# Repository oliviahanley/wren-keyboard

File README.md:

# Wren Keyboard

## Table of Contents
- [Introduction](https://github.com/oliviahanley/wren-keyboard#introduction)
- [2.0 Update](https://github.com/oliviahanley/wren-keyboard#2.0-update)
- [Controller](https://github.com/oliviahanley/wren-keyboard#controller)
- [PCB](https://github.com/oliviahanley/wren-keyboard#pcb)
- [Case and Plate](https://github.com/oliviahanley/wren-keyboard#case-and-plate)
- [Software](https://github.com/oliviahanley/wren-keyboard#software)
- [Cost Estimates and Purchasing](https://github.com/oliviahanley/wren-keyboard#cost-estimates-and-purchasing)
- [BOM](https://github.com/oliviahanley/wren-keyboard#bom)
- [Build Guide](https://github.com/oliviahanley/wren-keyboard#build-guide)

## Introduction
The Wren is a split ergonomic system keyboard. It takes heavy inspiration from the Lily58, [Afternoon Labs' Breeze](https://afternoonlabs.com/breeze/), and [SplitKB's Kyria](https://blog.splitkb.com/blog/introducing-the-kyria) with a Corne-ish layout.

Before this, my primary keyboard had been Prime Keyboards' prime_o, before which I used a handwired Planck. On both I made pretty heavy use of the numpad. I grew to appreciate the prime\_o's physical one, though, mostly because I spend a lot of time in Excel at my day job and like using the mouse and numpad simultaneously. I've been wanting to switch to ergo for a while, but I was annoyed by the thought of having to use a separate numpad to recreate that experience. This project was an attempt to solve that problem.

My original design simply incorporated a southpaw numpad. After some feedback, though, I decided to reinvent it as a more adaptable design. The repository includes a universal PCB (incorporating break-away tabs) and plates to make four boards, each reversible:
- A Lilly58/Kyria-inspired split board, with no extra keys;
- An extended layout with a 4x4 numpad;
- An extended layout with a traditional nav cluster; and
- A small 4x4 macropad (nicknamed Egg).

Each of these boards (besides the macropad) can be combined with the others in a split setup, so users can take their pick of a right or left nav cluster/numpad or combine both in the same board. You could even just use two of the basic boards together for a more traditional layout, though I'm sure there are more elegant designs out there for that.

## 2.0 Update
The 2.0 release includes several major changes, including:
- A 3D printable (or CNCable) case with two height variations
- Nice!Nano compatibility with battery plug and ZMK compatibility
- Nice!View support
- Support for hot-swap sockets in addition to soldered switches
- Choc v1 variant
- Optional display cover
- Better design and documentation for the Egg
- Flip-flop footprints for the MCU

## Controller
The Wren uses a Pro Micro-compatible footprint, but is designed around the Elite-C or nice!Nano's extra I/O pins. With just a Pro Micro, the outer column and nice!view won't work.

## PCB
The PCB uses reversible, MX and choc compatible footprints with hot-swap support.

The PCB is specifically designed around rotary encoders with a diameter less than 0.5". I'm using Kilo 50 sized knobs, but others in a similar size class will work well, too.

## Case and Plate
This repository includes a top and bottom plate designed around M2 screws and standoffs. The bottom plate can be manufactured out of FR4 PCB material by any manufacturer; this will likely be the most cost-effective option. The top plate cannot be manufactured by my preferred PCB fabricator, JLCPCB, but your milage may vary. Instead, I used the .eps files included in the [Case folder](https://github.com/oliviahanley/wren-keyboard/tree/main/Case) to have my top plates manufactured in stainless steel by SendCutSend. In my experience these plates are an extremely tight fit around Kailh Box switches, but considering these aren't hot-swap that's an acceptable trade-off for me.

To make a complete case, you'll need 7 M2 spacers (5 for the plain board), a top plate, and a bottom plate.

There's also a 3D-printed bottom case. This uses the top plate and PCB without the bottom plate. \<\<MORE HERE\>\>

## Software
Tested code for this board is in the [main QMK repository](https://github.com/qmk/qmk_firmware/pull/14570). Thanks so much to [noroadsleft](https://github.com/qmk/qmk_firmware/pull/16462) for getting QMK configurator working! To build a hex file with the default keymap, use the following code after setting up your [QMK build environment](https://docs.qmk.fm/#/newbs_getting_started):

```
qmk compile -kb wren -km default
```

This can be flashed to your keyboard [in the usual way](https://docs.qmk.fm/#/newbs_flashing). The push-button below the microcontroler will put the keyboard into DFU mode. 

When customizing your keymap, note that the matrix includes all keys that would be present in a numpad-numpad pair. In other words, even if the left side of your physical keyboard lacks a numpad, your keymap.c file will include those keys. Feel free to either mark all those keys with a KC_NO keycode or leave them as-is--it's not like you can press them anyway :). As well, if you'd like to plug your USB cable into the right half instead of the default left, add the following to your config.h:

```
#define MASTER_RIGHT
```

\<\<ZMK INFO HERE\>\>

## Cost Estimates and Purchasing <\<\UPDATE\>\>
It should be relatively affordable to have these boards manufactured. Here are my costs for my PCB components at JLCPCB in USD as of September 2021:
- Universal PCB (15 boards): $35.30
- Numpad bottom plate (5 boards): $14.50
- Nav bottom plate (5 Boards): $13.60
- Plain bottom plate (5 boards): $10.80
- Egg bottom plate (5 boards): $2.00

And for my plates from SendCutSend:
- Numpad top plate (2 plates): $62.38
- Nav top plate: $34.94
- Plain top plate: $26.08

The repository should include up-to-date zipped Gerber files, which can be used to have PCBs fabbed at your manufacturer of choice. I'm partial to JLCPCB (which consistently has very low prices and now offers aluminum PCB options for plates), but OSHPark is a good option if you're in the US and like purple or want single boards. For best compatibility, please have both plates and cases manufactured with a 1.6mm or 1.5mm thickness.

(I'm currently not planning on offering these boards as a kit. It should be cost-competitive to source the cases and plates yourself, and getting comfortable with ordering PCBs is a great first step to designing your own custom board. If you are interested in stocking this keyboard, though, please feel free to reach out and I'll be happy to provide any help I can.)

## BOM <\<\UPDATE\>\>
### Numpad Board
To assemble a numpad half, you'll need these parts:
- 1 Universal PCB
- 1 Numpad top plate
- 1 Numpad bottom plate
- 1 Elite-C microcontroller
- 7 8mm M2 threaded separators
- 14 4mm M2 screws
- 44 MX-style keyswitches
- 43 1u MX keycaps
- 1 2u MX keycaps
- 45 1N4148 diodes
- 1 Alps EC-11 compatible rotary encoder (Bourns PEC11L-4115F-S0020 recommended)
- 1 Rotary encoder knob (0.5" diameter or less)
- 1 2u PCB-mount cherry stabilizer
- 1 6mm push-button switch
- 1 PJ320E TRRS jack
- 2 4.7kΩ axial resistors

### Nav Cluster Board
To assemble a nav cluster half, you'll need these parts:
- 1 Universal PCB
- 1 Nav cluster top plate
- 1 Nav cluster bottom plate
- 1 Pro Micro compatible microcontroller
- 7 8mm M2 threaded separators
- 14 4mm M2 screws
- 38 MX-style keyswitches
- 37 1u MX keycaps
- 1 2u MX keycaps
- 39 1N4148 diodes
- 1 Alps EC-11 compatible rotary encoder (Bourns PEC11L-4115F-S0020 recommended)
- 1 Rotary encoder knob (0.5" diameter or less)
- 1 2u PCB-mount cherry stabilizer
- 1 6mm push-button switch
- 1 PJ320E TRRS jack
- 2 4.7kΩ axial resistors

### Plain Board
To assemble a nav cluster half, you'll need these parts:
- 1 Universal PCB
- 1 Plain top plate
- 1 Plain bottom plate
- 1 Pro Micro compatible microcontroller
- 7 8mm M2 threaded separators
- 14 4mm M2 screws
- 28 MX-style keyswitches
- 27 1u MX keycaps
- 1 2u MX keycap
- 29 1N4148 diodes
- 1 Alps EC-11 compatible rotary encoder (Bourns PEC11L-4115F-S0020 reccomended)
- 1 Rotary encoder knob (0.5" diameter or less)
- 1 2u PCB-mount cherry stabilizer
- 1 6mm push-button switch
- 1 PJ320E TRRS jack
- 2 4.7kΩ axial resistors

### Egg Macro Pad
To assemble an egg with a broken-off piece of a main board, you'll need these parts:
- 1 Universal PCB
- 1 Egg top plate
- 1 Egg bottom plate
- 1 Pro Micro compatible microcontroller
- 4 8mm M2 threaded separators
- 8 4mm M2 screws
- 12/16 MX-style keyswitches
- 12/16 1u MX keycaps
- 12/16 1N4148 diodes

## Build Guide <\<\UPDATE\>\>
_Please note that this build guide refers to the "top" or "bottom" of the PCB. Since the PCB is reversible, these terms are relative to the final orientation of the board, not anything absolute. For example, the top of the right hand board would be the bottom of the left-hand board._

0. If necessary, break off any unused sections of the PCB. This is best accomplished by placing the board on a hard, flat surface with the perforated section of the board placed over the edge. While holding the main section of the board to the surface, firmly press down on the section you'd like to detach until it breaks off. Then, use a file to remove any remnants of the perforation. 

1. Next, place diodes on the bottom side of the PCB, taking care to place the diodes with the black stipe facing the square pad.

TIP: Use needle-nose pliers to assist in bending diodes, as shown below.

2. Solder the diodes in place on the bottom side of the board.

3. Place the resistors on the bottom side of the PCB and solder them into place.

4. Turn the board over and clip the leads of the resistors and diodes as close as possible to the PCB. To avoid fitment issues with switches, ensure that the leads are cut nearly flush; nail clippers are good for this purpose.

5. Place the headers for the microcontroller in place with the plastic spacer at the front of the board and secure them with a piece of painter's tape, taking care that they are perfectly straight. 

Using the tape to ensure the headers remain straight, tack solder a pin on each strip.

Remove any remaining tape and solder the remaining pins.

6. Solder the controller to the headers on the front of the board. The controller should be facing down on the left half, and up on the right half. 

7. Place the reset button below the controller on the front of the board and solder it into place.

8. Place the TRRS jack on the front of the PCB and solder it into place.

9. Place the rotary encoder on the front of the PCB and solder it into place. Take care to ensure the encoder is as straight as possible; it is possible for the encoder to interfere with the plate if it's attached incorrectly.

10. Place the stabilizer.

11. Snap the switches into the plate, taking care to match the orientation of the PCB. They will likely be a tight fit.

12. Fit the switchplate onto the PCB, taking care to fit it around the encoder as shown.

13. Tack solder the switchplate into place using the switches on the corners of the board.

14. Finish soldering the switchplate.

15. Attach the knob for the rotary encoder.

16. Attach the standoffs using a screw through the front of the PCB.

17. Clean off any excess flux using isopropyl alchohol.

18. Using the standoffs, attach the rear plate to the board.

19. Attach rubber bumpers to the rear of the board for stability.

20. Admire your work! Your board is ready to be flashed. If necessary, repeat with the other side of the board.

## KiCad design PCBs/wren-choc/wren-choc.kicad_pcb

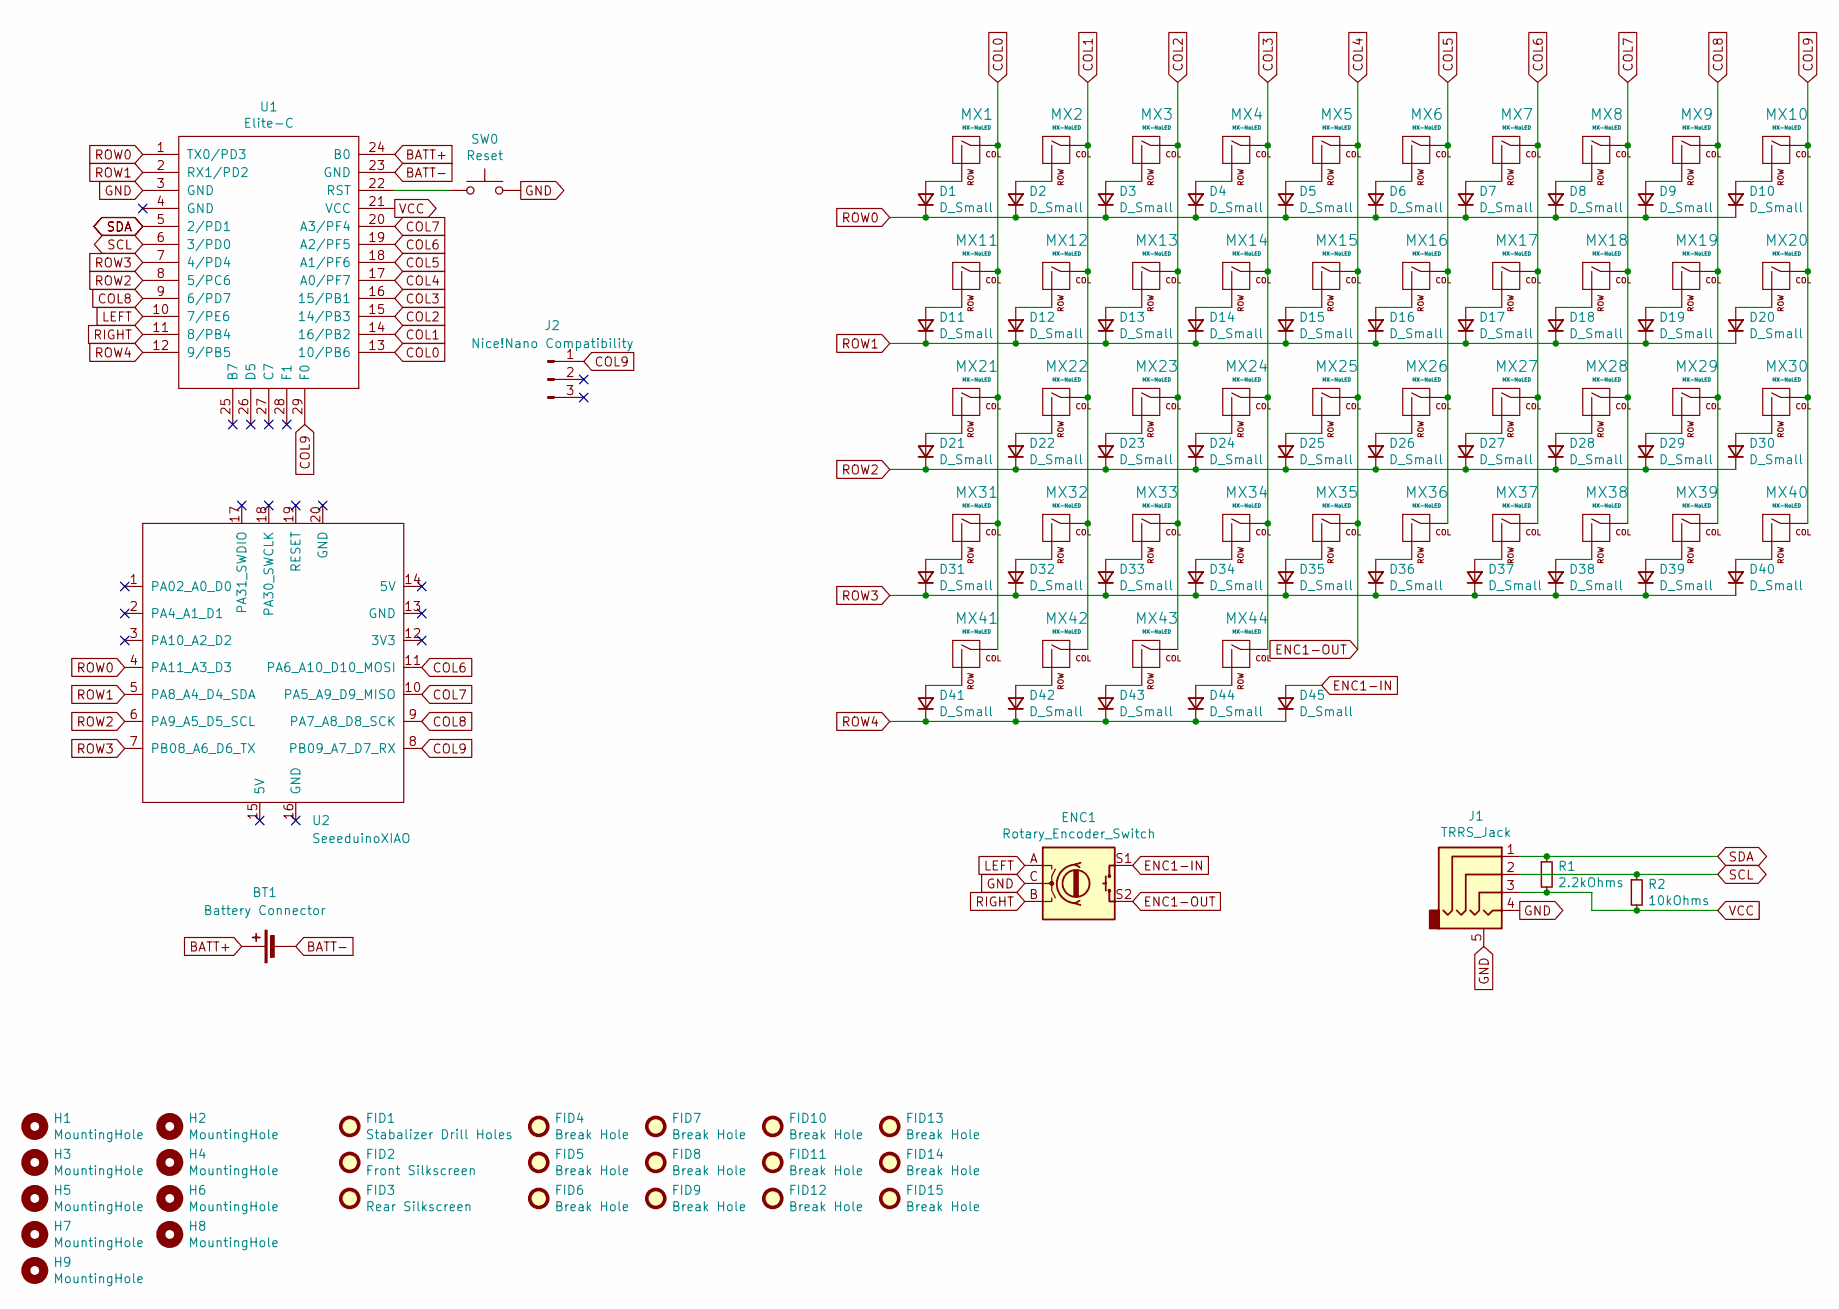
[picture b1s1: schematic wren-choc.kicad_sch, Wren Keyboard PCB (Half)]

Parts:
BT1: Battery Connector; PinHeader_1x02_P2.00mm_Vertical
D1, D2, D3, D4, D5, D6, D7, D8, D9, D10, D11, D12, D13, D14, D15, D16, D17, D18, D19, D20, D21, D22, D23, D24, D25, D26, D27, D28, D29, D30, D31, D32, D33, D34, D35, D36, D37, D38, D39, D40, D41, D42, D43, D44, D45: D_Small; D_SOD123_axial
ENC1: Rotary_Encoder_Switch; RotaryEncoder_Alps_EC11E-Switch_Vertical_H20mm
FID1: Stabalizer Drill Holes; Stabilizer_MX_2u
FID2: Front Silkscreen; wren_logo
FID3: Rear Silkscreen; wren_logo
FID4, FID5, FID6, FID7, FID8, FID9, FID10, FID11, FID12, FID13, FID14, FID15: Break Hole; MountingHole_2.1mm
H1, H2, H3, H4, H5, H6, H7, H8, H9: MountingHole; MountingHole_5.5mm
J1: TRRS_Jack; TRRS_JACK_MJ4PP9
J2: Nice!Nano Compatibility; PinHeader_1x03_P2.54mm_Vertical
MX1, MX2, MX3, MX4, MX5, MX6, MX7, MX8, MX9, MX10, MX11, MX12, MX13, MX14, MX15, MX16, MX17, MX18, MX19, MX20, MX21, MX22, MX23, MX24, MX25, MX26, MX27, MX28, MX29, MX30, MX31, MX32, MX33, MX34, MX35, MX36, MX37, MX38, MX39, MX40, MX41, MX42, MX43, MX44: MX-NoLED; SW_PG1350_choc_reversible
R1: 2.2kOhms; R_Axial_DIN0204_L3.6mm_D1.6mm_P5.08mm_Vertical
R2: 10kOhms; R_Axial_DIN0204_L3.6mm_D1.6mm_P5.08mm_Vertical
SW0: Reset; SW_PUSH_6mm
U1: Elite-C
U2: SeeeduinoXIAO; XIAO-RP2040

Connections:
BATT+: BT1.1 (+), U1.24 (B0)
BATT-: BT1.2 (-), U1.23 (GND)
COL0: MX1.1 (COL), MX11.1 (COL), MX21.1 (COL), MX31.1 (COL), MX41.1 (COL), U1.13 (10/PB6)
COL1: MX2.1 (COL), MX12.1 (COL), MX22.1 (COL), MX32.1 (COL), MX42.1 (COL), U1.14 (16/PB2)
COL2: MX3.1 (COL), MX13.1 (COL), MX23.1 (COL), MX33.1 (COL), MX43.1 (COL), U1.15 (14/PB3)
COL3: MX4.1 (COL), MX14.1 (COL), MX24.1 (COL), MX34.1 (COL), MX44.1 (COL), U1.16 (15/PB1)
COL4: ENC1.S2, MX5.1 (COL), MX15.1 (COL), MX25.1 (COL), MX35.1 (COL), U1.17 (A0/PF7)
COL5: MX6.1 (COL), MX16.1 (COL), MX26.1 (COL), MX36.1 (COL), U1.18 (A1/PF6)
COL6: MX7.1 (COL), MX17.1 (COL), MX27.1 (COL), MX37.1 (COL), U1.19 (A2/PF5), U2.11 (PA6_A10_D10_MOSI)
COL7: MX8.1 (COL), MX18.1 (COL), MX28.1 (COL), MX38.1 (COL), U1.20 (A3/PF4), U2.10 (PA5_A9_D9_MISO)
COL8: MX9.1 (COL), MX19.1 (COL), MX29.1 (COL), MX39.1 (COL), U1.9 (6/PD7), U2.9 (PA7_A8_D8_SCK)
COL9: J2.1, MX10.1 (COL), MX20.1 (COL), MX30.1 (COL), MX40.1 (COL), U1.29 (F0), U2.8 (PB09_A7_D7_RX)
ENC1-IN: D45.2 (A), ENC1.S1
GND: ENC1.C, J1.4, J1.5, SW0.2, U1.3 (GND)
LEFT: ENC1.A, U1.10 (7/PE6)
unnamed: D1.2 (A), MX1.2 (ROW)
unnamed: D2.2 (A), MX2.2 (ROW)
unnamed: D3.2 (A), MX3.2 (ROW)
unnamed: D4.2 (A), MX4.2 (ROW)
unnamed: D5.2 (A), MX5.2 (ROW)
unnamed: D6.2 (A), MX6.2 (ROW)
unnamed: D7.2 (A), MX7.2 (ROW)
unnamed: D8.2 (A), MX8.2 (ROW)
unnamed: D9.2 (A), MX9.2 (ROW)
unnamed: D10.2 (A), MX10.2 (ROW)
unnamed: D11.2 (A), MX11.2 (ROW)
unnamed: D12.2 (A), MX12.2 (ROW)
unnamed: D13.2 (A), MX13.2 (ROW)
unnamed: D14.2 (A), MX14.2 (ROW)
unnamed: D15.2 (A), MX15.2 (ROW)
unnamed: D16.2 (A), MX16.2 (ROW)
unnamed: D17.2 (A), MX17.2 (ROW)
unnamed: D18.2 (A), MX18.2 (ROW)
unnamed: D19.2 (A), MX19.2 (ROW)
unnamed: D20.2 (A), MX20.2 (ROW)
unnamed: D21.2 (A), MX21.2 (ROW)
unnamed: D22.2 (A), MX22.2 (ROW)
unnamed: D23.2 (A), MX23.2 (ROW)
unnamed: D24.2 (A), MX24.2 (ROW)
unnamed: D25.2 (A), MX25.2 (ROW)
unnamed: D26.2 (A), MX26.2 (ROW)
unnamed: D27.2 (A), MX27.2 (ROW)
unnamed: D28.2 (A), MX28.2 (ROW)
unnamed: D29.2 (A), MX29.2 (ROW)
unnamed: D30.2 (A), MX30.2 (ROW)
unnamed: D31.2 (A), MX31.2 (ROW)
unnamed: D32.2 (A), MX32.2 (ROW)
unnamed: D33.2 (A), MX33.2 (ROW)
unnamed: D34.2 (A), MX34.2 (ROW)
unnamed: D35.2 (A), MX35.2 (ROW)
unnamed: D36.2 (A), MX36.2 (ROW)
unnamed: D37.2 (A), MX37.2 (ROW)
unnamed: D38.2 (A), MX38.2 (ROW)
unnamed: D39.2 (A), MX39.2 (ROW)
unnamed: D40.2 (A), MX40.2 (ROW)
unnamed: D41.2 (A), MX41.2 (ROW)
unnamed: D42.2 (A), MX42.2 (ROW)
unnamed: D43.2 (A), MX43.2 (ROW)
unnamed: D44.2 (A), MX44.2 (ROW)
unnamed: SW0.1, U1.22 (RST)
RIGHT: ENC1.B, U1.11 (8/PB4)
ROW0: D1.1 (K), D2.1 (K), D3.1 (K), D4.1 (K), D5.1 (K), D6.1 (K), D7.1 (K), D8.1 (K), D9.1 (K), D10.1 (K), U1.1 (TX0/PD3), U2.4 (PA11_A3_D3)
ROW1: D11.1 (K), D12.1 (K), D13.1 (K), D14.1 (K), D15.1 (K), D16.1 (K), D17.1 (K), D18.1 (K), D19.1 (K), D20.1 (K), U1.2 (RX1/PD2), U2.5 (PA8_A4_D4_SDA)
ROW2: D21.1 (K), D22.1 (K), D23.1 (K), D24.1 (K), D25.1 (K), D26.1 (K), D27.1 (K), D28.1 (K), D29.1 (K), D30.1 (K), U1.8 (5/PC6), U2.6 (PA9_A5_D5_SCL)
ROW3: D31.1 (K), D32.1 (K), D33.1 (K), D34.1 (K), D35.1 (K), D36.1 (K), D37.1 (K), D38.1 (K), D39.1 (K), D40.1 (K), U1.7 (4/PD4), U2.7 (PB08_A6_D6_TX)
ROW4: D41.1 (K), D42.1 (K), D43.1 (K), D44.1 (K), D45.1 (K), U1.12 (9/PB5)
SCL: J1.2, R2.1, U1.6 (3/PD0)
SDA: J1.1, R1.1, U1.5 (2/PD1)
VCC: J1.3, R1.2, R2.2, U1.21 (VCC)

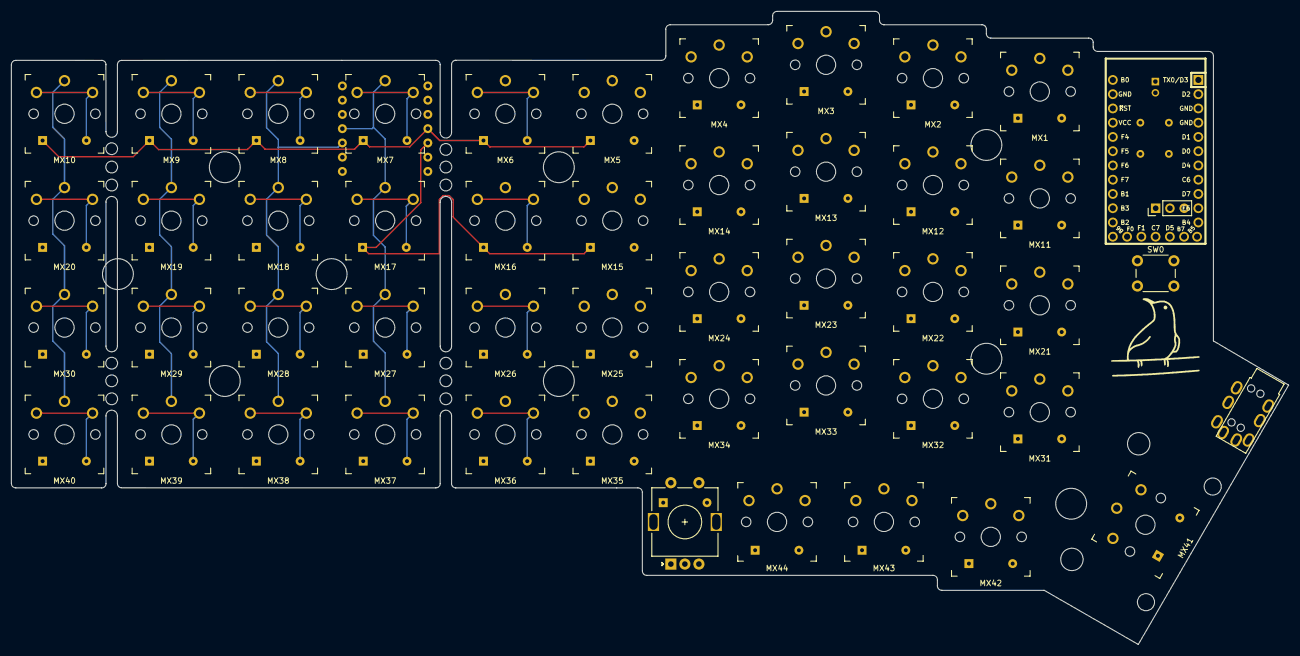
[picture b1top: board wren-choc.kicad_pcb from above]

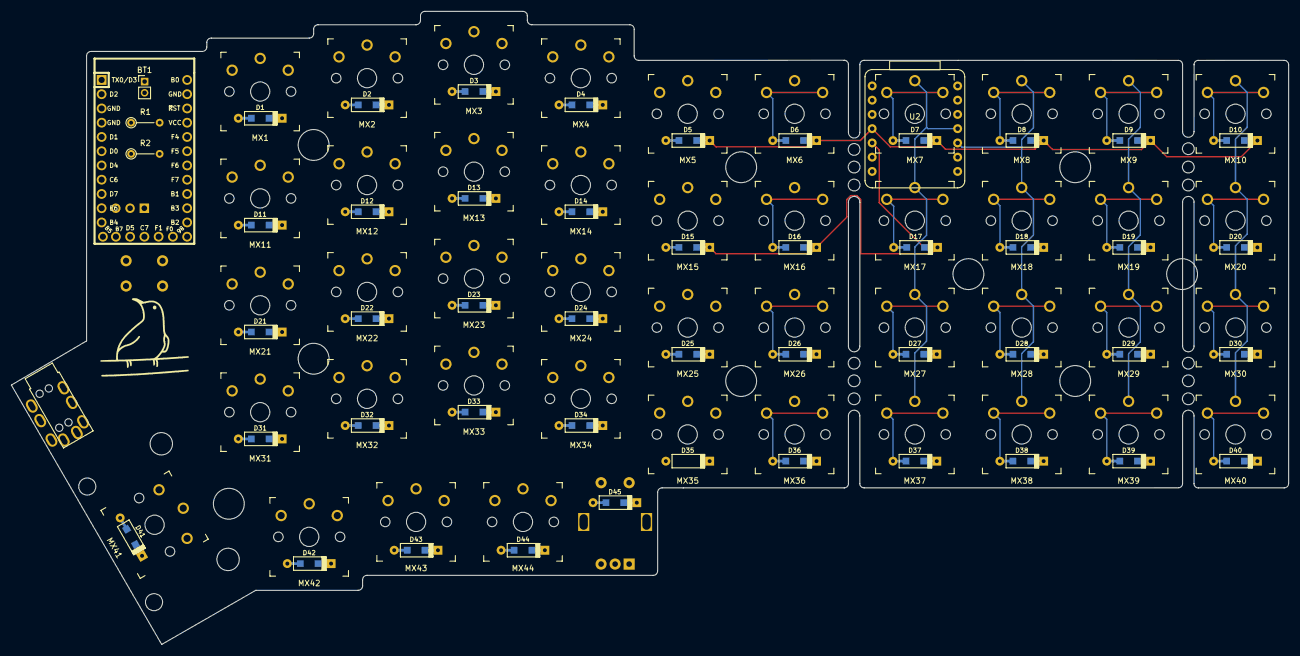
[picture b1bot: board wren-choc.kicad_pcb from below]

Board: 2 copper layers, 227.7 x 112.8 mm, 122 parts (51 on the bottom side), 69 nets.

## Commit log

2021-04-09 Create KiCad Project
2021-04-10 Add footprint submodules.
2021-04-10 Import footprint and schematic libraries to project.
2021-04-10 Add Pro Micro Footprint
2021-04-10 Refactor Left PCB
2021-04-10 Finish Left-Hand Schematic
2021-04-11 Routing Half-Finished
2021-04-11 Tracks Finished
2021-04-11 Left Side Finished
2021-04-11 Added Mirrored Right PCB
2021-04-11 Wrap up for the day
2021-04-11 Add encoder to right side of schematic
2021-04-11 Cleaner Track Routing, Remove Encoder
2021-04-11 Add PCB Mount Holes
2021-04-13 Switch to Elite C Footprints
2021-04-13 Create wren-right 2.kicad_pcb-bak
2021-04-13 Add Encoders to PCB
2021-04-14 Component Updates
    Switch to through-hole diodes and resistors, reroute traces, etc.
2021-04-14 Cleanup Work
2021-04-16 Cleanup, re-add drill holes
2021-04-16 First Pass on Left Plate
2021-04-17 Reposition Rotary Encoder and Create New Right Board
2021-04-18 Various Updates
    New plates, updated routing on the right side, assorted other changes.
2021-04-18 Add Wren Logo (Pt. 2)
2021-04-18 Add Bottom Plates, SVG for Case
2021-04-18 .DS_Store banished!
2021-04-18 Add Initial readme.md
2021-04-18 Update LICENSE
2021-04-19 Adopt Kyria-like stagger on right half
2021-04-19 Revert "Update LICENSE"
    This reverts commit a53699f9cfbd3209461f3a40c804e176d484cb1a.
2021-04-19 Revert Kyria stagger (for now)
2021-04-20 Add Gerber files
2021-04-20 Use insight on rotary encoder position to adopt more Kyria-like stagger
2021-04-23 Finish left side kyria-like stagger
2021-04-24 Finalize encoder position on left side
2021-04-25 Add increased stagger to right side
2021-04-25 Update top and bottom plates, ReadMe
2021-04-25 Add Images
2021-04-25 Add more text
2021-04-25 Add plate pictures, remove outdated Gerbers
2021-04-25 Start on right-side nav variant
2021-04-25 Update preview image
2021-04-25 Switch to reversible footprints, add nav variant
2021-04-25 Wrap up remainder of system update
2021-04-25 Add Gerbers
2021-04-26 Quick nav update
2021-04-26 Standardize MCU Pins
2021-04-27 Make initial changes and place break-off holes
2021-04-27 Continue working
2021-04-27 Finish universal PCB and prepare for merge
    Finished up the universal PCB (with breakoff tabs) and moved old individual PCBs to the legacy folder
2023-11-17 Rebase
2024-10-23 Add Nice!Nano compatibility
2024-10-23 Add battery header, update readme
2024-10-23 Minor labeling changes
2024-10-23 Update README.md
    Rough draft, please do not take the 2.0 feature list as any sort of promise.
2024-10-24 Move old univeral PCB to the legacy folder
2024-10-24 Specify that existing files are for MX switches in anticipation of future choc variant
2024-10-24 Add new folders
2024-10-24 Add placeholder files
2024-10-31 Add first draft of choc board, move to Seeed Xiao on Egg.
2024-10-31 Updates to choc board.
